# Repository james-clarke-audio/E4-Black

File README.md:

# E4 — "E4-Black"

An **STM32F411 micromouse**: a C++ port of the ukmars
[**mazerunner-core**](https://github.com/ukmars/mazerunner-core) firmware onto
custom hardware, with a **Web Bluetooth** companion app for live telemetry,
control and calibration. Built for the October 2026 micromouse competition.

> **Status:** active development — hardware bring-up and sensor calibration.

## Features

- **1 kHz control loop** (SysTick) — motion, sensing and the search brain all
  run deterministically.
- **IR wall sensing** — four emitter/detector pairs, ambient-subtracted with a
  batched dark-then-lit read. Two forward sensors (front wall) and two diagonal
  sensors (side walls / centring).
- **Gyro heading** — the gyro holds heading; the side sensors handle lateral
  position and wall presence. Gyro scale is **calibrated on the floor and
  persisted to EEPROM**, not compiled in — it is a property of the individual
  MPU-9250 and shifts with temperature, so it can be re-measured at a venue
  with nothing but the companion app.
- **On-board UI** — SSD1306 OLED with a two-button menu; the whole menu is also
  drivable over Bluetooth.
- **Bluetooth telemetry & control** via the companion app — a Control tab for
  watching and driving her, and a Tuning tab for setting her up: live IR
  monitor, an emitter-hold camera aid for aiming, live turn tuning (gyro-closed
  spins & arcs), and firmware-version reporting.
- **Non-blocking wall sampling** (opt-in) — a five-state sampler ticked from the
  control ISR returns a full ambient-subtracted set every 5 ms with no
  busy-wait, so the wall flags stay live while she's moving.
- **Maze persistence** to on-board EEPROM.
- **Flood-fill search / speed run** from mazerunner-core, with a virtual/real
  sensor switch so the brain can be exercised in simulation.
- **A route executor** — one walk that either drives a planned route or
  rehearses it, so the rehearsal proves the sequencing the driver uses.
- **Time-weighted route planner** — least time rather than fewest cells, with
  diagonals *searched* rather than substituted, and an optimistic twin of each
  plan that says how much is still left to find.
- **Wall follower**, both hands, driven and simulated — its own competition
  class rather than a fallback solver.
- **A simulator that runs at the speed the motion model predicts**, so a
  simulated run takes as long as it claims to and the two numbers can be
  compared. Playback can be sped up for watching; the reported figure never
  moves with it.
- **A maze editor in the companion app** — draw a course on the big canvas,
  save it as text or `.maz`, and send it straight to her. Quicker than hunting
  through 406 files for one that exercises the thing you are testing.

## Hardware

- **MCU:** STM32F411CEU6 (Cortex-M4F, "Black Pill"-class).
- **Wall sensors:** 4× IR pairs — TSAL6100 emitters (940 nm) into OP505A
  phototransistors; emitters switched low-side by FDV301N MOSFETs from a 5 V
  rail. (The original board carried SFH4550; the sensor assemblies now fitted
  are TSAL6100.)
- **Display / storage:** SSD1306 OLED and a 24LC256 EEPROM, both on I2C1.
- **Drive:** DRV8833 motor driver, plus a gyro for heading.

Full pin map, sensor geometry and housing detail are in the reference manual
(see below).

## Build & run

- **Firmware:** STM32CubeIDE (2.2 / GCC 14). Import `Source/` as an existing
  project, build the **Debug** config, and flash over ST-Link to the
  STM32F411CEU6.
- **Companion app:** open `e4-maze.html` in a Web Bluetooth browser — Chrome or
  Edge on desktop, or an iPad via a WebBLE browser such as Bluefy (iOS Safari
  has no Web Bluetooth). Pair over BLE to monitor the sensors, drive the menu,
  and read the running firmware version.
- **Hosted copy:** the repo publishes to GitHub Pages, so the current app is
  always live at
  [`/E4-Black/e4-maze.html`](https://james-clarke-audio.github.io/E4-Black/e4-maze.html)
  and the manual at [`/E4-Black/docs/`](https://james-clarke-audio.github.io/E4-Black/docs/).
  Web Bluetooth needs a secure context, so on a tablet this is the route to use
  rather than copying the file across.

## Documentation

The **E4 Reference Manual** lives in [`docs/`](docs/index.html) — open
`docs/index.html`. Eleven chapters: overview, architecture & pin map, sensor
aim, sensor geometry, sensor housing, the firmware/menu map, position integrity
("Staying Located"), a design note for the next board (STM32G474), how she
chooses her path, the turn table, and the sensor carrier.

## Repository layout

| Path | What it is |
|------|-----------|
| `Source/` | STM32CubeIDE firmware project (Core / Drivers / Modules / Program). |
| `CompanionApp/` | Native SwiftUI companion (macOS/iPad) + the `E4Core` package — **the tool she is driven from**. |
| `e4-maze.html` | Web Bluetooth companion app (single file); follows the Swift app rather than leading it. |
| `docs/` | The reference manual (`index.html` + chapters). |
| `3D Files/` | Sensor housings, wheels, mounts, and the sensor socket plate (STL, print notes, and the parametric source that generates and verifies it). |
| `tools/planner-bench/` | Native build of the route planner, for scoring routes against the maze files without a robot. |
| `tools/bench-mazes/` | Finds and writes the per-turn tuning rigs, and checks the shipped files by planning them. |
| `mazefiles/` | 408 real competition mazes, binary and text, plus `bench/` — twelve single-corridor tuning rigs. |
| `E4-cell-alignment-A4.pdf` | 1:1 print jig for squaring a test cell. |

See [CONTRIBUTING.md](CONTRIBUTING.md) for the fuller layout and workflow.

## Contributing

`main` is protected: collaborators work on a branch and open a pull request.
Details, commit style and the firmware-version convention are in
[CONTRIBUTING.md](CONTRIBUTING.md).

## Credits

Firmware is a port of Peter Harrison's ukmars **mazerunner-core**. Thanks to the
UK micromouse community.

## License

Released under the [MIT License](LICENSE) — © 2022 Peter Harrison
(ukmars mazerunner-core), © 2026 James Clarke. E4 is a derivative of the
MIT-licensed mazerunner-core and keeps the same terms.

---

## Firmware releases

`FW_VERSION` lives in `Source/Program/inc/version.h`, shows on the OLED splash
and is reported over Bluetooth (`VER?`). **Minor** for a feature, **patch** for
a fix. **1.0.0 is reserved** for the build that goes to the October competition
— everything before it is bring-up.

Each entry names the firmware commit; companion-app and docs commits that
landed alongside are listed after it, since the two move together. Newest
first.

**0.34 — 18 Sep 2026 · The post loop**
From an old lab note of James's: drive into a cell, then round a post
continuously, watch the centre drift and adjust α. It is a better rig than the
zigzag, and one line of geometry says why.

**Four chained same-hand 90s of radius 90 *are* a circle centred on a post.**
She comes up the lane at x = 90 turning right; the arc centre sits 90 mm to her
right, which is the post. After the quarter she is heading east and her right is
now south — the same point. Every quarter shares a centre, so the four are one
circle, 565.5 mm round.

Which pins ω: `R = v/ω`, so R = 90 at 300 mm/s needs **191 °/s** — the figure
`SS180` already holds, because its lateral step of 2R is also one cell. And it
reconciles the two numbers in Ch 10: **226 is the figure for a turn driven on
its own**, where ω ramps to zero at the end and the trapezoid swings wider than
the ideal circle. Driven continuously there are no ramps between the quarters,
so the ideal `R = v/ω` applies and 191 is simply right. Two manoeuvres, two
answers, and the loop is the one that matches what a chained turn has to be.

**It separates ω from α.** Over a closed lap the four local frames sit at 0°,
90°, 180° and 270°, so any consistent per-turn displacement error sums to zero —
radius, offsets, tangential lag alike. Heading does not: the frames precess, the
lap stops closing, and the centre walks by about `2.83·|d|·ε`.

| error per turn | drift per lap | after 8 laps |
|---|---|---|
| 0.1° | 0.6 mm | 5 mm |
| 1.0° | 6.3 mm | 50 mm |

So ω sets the *size* of the circle and α sets the *drift* of its centre. It is
also the honest gyro-scale test — at running speed with the wheels rolling
rather than scrubbing in place — and the two causes separate, since scale error
is speed-independent while α's grows with ω. Odometry gives the radius back for
nothing: arc distance over 2π·laps, reported as `R_meas` beside the 90 it wants.

`Post loop` (Calibration, or BT `A`), set up by `LOOP,laps,ω,α,hand,speed`. It
is its own menu action rather than another use of `ARC` because **1440° is not a
turn** and writing it into a row would ruin the row.

*Alongside:* page 15 of `E4-bench-diagnostics-A4.pdf` draws the rig — a 2×2
block with the middle post free-standing, the 90 mm circle to mark round it, the
tangent run-in, and what a degree per turn looks like after one, four and eight
laps. Her outline on every page is now the real one: the chassis board is 77
wide with wheel wells stepping in to 11.46/65.54, 100 long with a semicircular
nose of radius 38, and the axle 35 mm from the back — all of it already written
down in Ch 11, Ch 4 and `config.c`.

**0.33 — 18 Sep 2026 · The approach is part of the turn**
A tuning run is *drive to the turn, make it, drive out* — and the first of those
three was the one the tuner could not be asked for. `ARC`'s fifth field writes
`entry_offset`, and `run_arc_from_table()` passed `entry_offset` straight in as
the lead-in, so the arc always began that many millimetres after she started
moving. Fine for "does this arc look right"; useless for "does she come out of
it in the lane", which is the only question a bench answers.

The approach is now counted in cells and the millimetres derived:

| entered from | lead-in |
|---|---|
| a straight | `BACK_WALL_TO_CENTER + cells × FULL_CELL − entry_offset` |
| the diagonal | `cells × DIAG_PITCH − entry_offset` |

`DS45`, `DS135` and `DD90` begin **on** the diagonal, where the pitch is 127.279
and there is no back wall to square up on — she is placed on the line by hand.
Which case applies follows from the row rather than from a switch someone has to
remember: a turn that leaves the diagonal is a turn that was already on it.
`POS,<cells>` sets it, `TUNE,pos=,lead=,pitch=` reports what she will actually
drive *before* anything moves, and `TURNRES` carries the row and the lead so a
log line three runs back still means something.

**The card does the arithmetic before she does.** `R = v / ω`, and an arc joining
two lanes that cross at θ is tangent to both only at `R·tan(θ/2)` either side of
the crossing. There is one wrinkle, and it took drawing the maze out 1:1 to see
it: `entry_offset` is measured back from the **lattice point** the planner books
the turn at, which for most turns is also where the two lanes cross — but an
`SD45` is booked in at a **cell centre**, while a straight lane meets a diagonal
at the **wall midpoint 90 mm earlier**. That half cell is part of the offset.

| row | ω | R at 300 | tangent | + half cell | needs | has | |
|---|---|---|---|---|---|---|---|
| SS90E | 170 | 101 | 101 | — | 101 | 100 | agrees |
| DD90 | 273 | 63 | 63 | — | 63 | 63 | agrees |
| **DS45** | **95** | **181** | **75** | **—** | **75** | **120** | **does not** |
| **SD45** | **95** | **181** | **75** | **90** | **165** | **120** | **does not** |

So the two 45 rows cannot both be right while they share a number — one needs
165 and the other 75. The same 120 sits in the planner as `sd45_offset` /
`ds45_offset`, so those move with them. The Tuning screen shows the gap and
offers the figure; the floor decides which of the numbers was wrong, but it
cannot until they agree.

One number says it best: a diagonal step is 127.3 mm and `ds45_offset` is 120 of
it, so on `bench-3x3-45min` the DS45 gets **seven millimetres** of approach
before the arc starts. At the tangent value it gets 52. That is why the planner
abandons that geometry and drives `ARC_R, SPIN_L` instead.

*Alongside:* `E4-bench-diagnostics-A4.pdf` — the 1:1 cell template (centrelines,
corner-to-corner, and the diamond joining the four wall midpoints that is the
actual diagonal lane), plus a page per hand showing where the mouse gets put
down. `06fc12d` and `fa6d585` — `mazefiles/bench/`, twelve single-corridor
tuning rigs, and `tools/bench-mazes/` which found them by enumerating every
corridor that fits in a section and asking the real planner what each one
produces. Two results fell out of that search. A 3×3 entered at (0,0) facing
north can only turn right first, because the west perimeter is beside her —
`SD45_L` is unreachable there without a spin. And **(2,0) facing north is the
mirror image of (0,0) facing north**, so once the start pose is allowed to move,
every left-hand rig is the x-mirror of its right-hand twin, walk for walk.

**0.32 — 18 Sep 2026 · She can finish by turning into the goal**
Every goal test in `plan_native()` sat inside the cell-expansion loop, which
advances a cell *before* it looks. So a route that **arrives** at the goal by
turning into it was never recognised as finished: she drove past and came back,
or took a longer way round that happened to approach along a straight.

The node's own cell is now tested before the loop, with `best_cells = 0` and
`best_t = 0` because the turn that brought her there is already paid for in
`key`. `step_time()` returns `0.0f` for a zero-cell goal step rather than asking
`straight_time()` for a negative distance — the clock stops on *entering* the
goal, and what is left of that cell afterwards is not on it.

On Boston the last vertices went from `DS45_L (17,18) → (17,17) → GOAL (17,15)`
to `… → GOAL (17,17)`. Swept over the whole 394-maze corpus: **72 faster, 320
unchanged, 2 slower, 0 invalid**, mean 32.864 → 32.761 s. Best: japan1997f
−3.460 s, uk1992q −2.698 s, boston −1.544 s.

The two slower ones are not a regression in the fix. `key_of()` quantises time
to centiseconds — that is what makes Dial's bucket queue O(E) — so routes tying
on the quantised key can differ by up to ~10 ms a step, and ≤0.13 s over twenty
steps is inside one bucket width. Recorded here so nobody hunts it later.

**0.31 — 18 Sep 2026 · No toy maze at boot, and the editor can undo**
The boot scaffold seeded a two-cell maze with the goal at (1,1). It made a whole
class of mistake invisible: a Plan route run with **no maze sent** looked
entirely successful, because there really was a maze and she really did solve
it. She now boots with `maze.h`'s own `m_goal{7, 7}` and an open arena as ground
truth, so a run with nothing sent looks like what it is.

The companion app's maze editor grows undo — `history: [E4MazeFile]` with
`canUndo` / `undo()`, and ⌘Z on the canvas.

**0.30 — 17 Sep 2026 · She speeds up through ground she has already covered**
Watching a simulated explore, she never went any faster in cells she had already
been through — and she didn't, in either the simulator or the firmware.
`sim_move_seconds()` used `FULL_CELL / SEARCH_SPEED` for every cell, and
`search_to()` crawls at `SEARCH_SPEED` from the first cell to the last. The
simulator was faithfully showing what the firmware does, which is the simulator
doing its job.

**The test is per cell, not per leg.** The obvious version of this is to run the
whole return leg fast, on the grounds that she has just driven it. That is
wrong: the flood picks the best *known* path home and known does not mean
*visited* — she will have seen a cell's walls from next door without ever
entering it, and those cells are exactly where there is still something to
learn. So the return leg becomes an exploring run that happens to be quick in
the parts already covered.

`cruise_speed()` is that rule, in one place, used by the driven search and the
simulated one so neither models something the other does not do:

| condition | speed |
|---|---|
| the cell she is **entering** is fully visited, **and** the move out of it is straight | `RUN_SPEED` |
| anything else | `SEARCH_SPEED` |

The second condition is the one that is easy to forget. There is no room to shed
speed between a cell's sensing point and the turn point after it, so carrying run
speed into a turn means entering it too fast. Checking costs nothing: in visited
territory the map is complete, so `heading_to_smallest()` on the flood she
already has is a reliable one-cell look ahead.

**And a sloppy read at speed cannot hurt her**, which is what makes this safe
rather than merely fast. She still senses and still calls `update_map()` in a
cell crossed at 600 mm/s — but `update_wall_state()` refuses to change a wall
that has already been seen, and *fully visited* means every wall in that cell
has been. A bad reading is discarded by construction, in exactly the cells where
the rule allows speed. The only place a wrong wall could be written is a cell
with something unknown in it, and those are the cells she is required to crawl
through.

`sim_move_seconds()` now tracks the speed she is **carrying** and costs each move
with `timing::straight_time` — the planner's own model — so a run of visited
cells visibly winds up and the cell before a turn visibly sheds it, instead of
every cell costing a flat 0.6 s.

The wall follower stays at search speed throughout, deliberately: `cruise_speed()`
reads the flood to look ahead, and a follower never floods.

**0.29 — 17 Sep 2026 · The executor left a diagonal by the wrong side**
A diagonal speed run finished at **(1,0)** — near the start, nowhere near the
goal — having walked a staircase west and south with no 45° heading in it, on a
route whose time came back exactly right at 23199 ms.

One line. `run_route` left a diagonal with `nh = (L) ? ((dd + 3) & 3) : ((dd + 1) & 3)`.
"+3 to turn left" is correct *inside* an enum. This crosses from `Diag` to
`Head`, and those are different enums offset by half a turn: leaving a diagonal
to the left is **+0** and to the right is +1. The right hand was accidentally
correct, which is why it took a real route to expose.

What it does is worse than a wrong heading: it lands her on a **post**, the one
lattice point that is never occupied, so her half-cell coordinates lose their
parity and every orthogonal move afterwards keeps her on the wrong parity for
the rest of the route. Hence a whole run animated on the lines *between* cells —
which is exactly what the `POS` trail showed, every coordinate an even multiple
of 90.

Fixed in **one place, not two**: `diag_ccw`/`diag_cw` move from statics in
`native.cpp` to inline functions in `native.h`, so the executor uses the same
mapping `route_points()` does rather than a second copy of it. Two copies of that
mapping is how one of them went wrong.

And the walk checks itself now. A route ends at a cell **centre**, odd in both
half-cell coordinates; anything else means the walk lost the lattice and every
cell it has reported since is fiction. It says so — `SR,LOST u= v= diag=` —
rather than reporting a plausible wrong answer.

Verified on the maze that broke it: every vertex of the run now matches the
planned route exactly, and she finishes at (8,8).

**0.28 — 17 Sep 2026 · The route executor**
The planner has been able to answer since 0.20 and nothing acted on the answer.
`run_route()` does.

**One walk serves both the real run and the rehearsal.** The part worth getting
right is the sequencing — which turn, after how many cells, from which heading —
and a simulator that sequenced differently from the driver would prove nothing
about the driver. The only thing the `simulate` flag changes is whether a step
is animated or driven.

Timing comes from a new `route_times()` in `diagonal.cpp`, which walks the route
with the **same `step_time()` that costed it** and reports each step split into
the run before the turn and the turn itself. That split is what lets the
rehearsal animate a step at its true duration, and it means the simulated total
equals `route.seconds` by construction rather than by coincidence.

    Sim speed run   F    plan, then rehearse at the speed the model predicts
    Speed run       l    plan, then drive
    KIND,<0|1|2>         shortest · quickest · quickest with diagonals

Which route is a **setting** rather than three menu entries, because the three
are one run with a different cost function and the point is comparing them back
to back on one maze. The default is quickest orthogonal: the diagonal route is
faster on paper, but every diagonal row of the turn table is arithmetic that has
never met a floor.

Both actions **stream the route before executing it**, so the line she is about
to take is on screen before she takes it, and a run that goes wrong can be
compared against what she meant to do rather than against memory.

One simplification, named in the code rather than hidden: in the simulated turn,
position advances during the run and heading rotates at the vertex, so an arc
looks like a spin on screen. The *time* is right either way and the route line
shows the true path — but the animation is not evidence about arc geometry.
**Zigzag test** is what answers that.

> `act_speed_run` is **unproven**. No part of the driven path has been near a
> floor, and the turn table it reads is arithmetic outside the two SS90E rows.
> It arms and waits like everything else; give her room.

**0.27 — 17 Sep 2026 · The followers arm like everything else, and say so**
Two bugs, both from 0.25. `follow_to()` **did not wait** — every other action
that turns a wheel calls `sensors.wait_for_user_start()` before it moves, and
the driven wall follower went straight from a tap in the app to driving. It arms
now, and so does the simulated twin, so both halves of the pair behave the same
way and neither teaches a habit the other punishes.

The four followers were also missing from `waitsForButtonPress`, which is why
pressing one in the app looked like nothing happening: she printed
`armed: press a button to launch` and blocked, correctly, and the app had no way
to tell a deliberate pause from a dropped command. Both apps now put that
message in front of you rather than leaving it as one line among hundreds, and
the **Actions** screen gets the same armed banner the maze screen already had —
it had been showing `Running:` for an action doing nothing of the sort.

**0.26 — 17 Sep 2026 · The simulator runs at the speed the model predicts**
`sim_step` animated eight frames of thirty milliseconds whatever the move, so a
cell crossing, a 90 and a dead-end reversal all took 240 ms and the simulator
told you nothing about time. It takes a **duration** now and the frames follow
from it, and that duration comes from `timing.h` — the planner's own model, not
a second one written for the animation, so the two cannot drift into different
opinions about the same mouse.

| move | cost |
|---|---|
| `AHEAD` | one cell at search speed |
| 90 | an **arc**: she rotates *while* she travels, so it is whichever of the two takes longer, not the sum |
| `BACK` | the one move that does not overlap — `turn_back()` stops dead, spins on the spot and moves off again, so that one adds up |

Getting the 90 wrong the other way is how a simulator flatters a route full of
corners; getting `BACK` wrong is how it flatters one full of dead ends.

The reported time is now the **modelled** clock, not `HAL_GetTick()`. The two
agree to within the odd frame, which is exactly why the wall clock must not be
the one reported — a slow link or a stalled frame would read as a slower mouse,
and the figure would stop being a property of the route. Real search runs are
untouched; there the wall clock *is* the truth.

Two details decide whether it is honest. The frame deadline **absorbs** transmit
time rather than adding to it (a `POS` and `TEL` pair is about 56 bytes, roughly
10 ms of wire at 57600, so delaying a full frame on top would run every run a
third slow). And `SIM_RATE` — `SIM,<rate>` over BT, a picker in both apps —
scales the *watching* only, because a real-time explore is forty-odd seconds and
nobody should sit through that twice, but the number she reports must not move
when you skip ahead.

**0.25 — 17 Sep 2026 · The wall follower, both hands, driven and simulated**
`follow_to()` had been sitting in `mouse.h` implementing a left-hand follower the
whole time, with `act_wall_follow` still an `act_todo` stub, so nothing could
reach it. It takes a hand now:

    20  Wall follow L   w        32  Wall follow R   W
    33  Sim follow L    q        34  Sim follow R    Q

Four entries rather than one action with a hand setting, because the hand *is*
the experiment — left and right walk different halves of a course. The
simulated pair animate the same decision with the motors never armed, so both
hands can be run against any maze file with no bench at all.

**A wall follower is its own competition class, not a weaker solver.** A
follower course is built with a wall connected all the way to the centre, so a
follower always arrives — that is the point of the event. A maze-solver maze is
built the other way round, with the inside deliberately disconnected from the
outside, so a follower can never reach the middle of one however long it walks.
Same code, two events.

So `FOLLOW_STEP_LIMIT` (512, four times the cells in the arena) is not a guard
against a weak algorithm — on its own course it never trips. It exists because
this code gets pointed at a solver maze in the simulator, where **not arriving
is the correct answer**, and the only wrong behaviour would be walking for ever
while that is true. Giving up reports `WF,gave up after N cells (left hand)`.

Of the **406** files in `mazefiles/binary`, **90 are follower-solvable and 316
are not** — and it is the *same* 90 for both hands, with not one maze yielding
to one hand and not the other. That is structural rather than luck: the hand
decides which route she walks, not whether the centre is reachable. If the
centre's walls are connected to the perimeter, both hands are walking the same
wall component; if it is an island, neither can. Five of the 90 are built for
the class explicitly — `uk2010follower`, `uk2011follower-final`,
`tic05followersheats`, `robotic-2011-follower-heats`, `-finals` — and 33 are
competition mazes including `japan1991`, `uk2003q` and `uk2009f`. `test3.maz`
arrives in 14 cells if you only want a smoke test.

**0.23 — 16 Sep 2026 · How much of the route is still guesswork**
"Have I explored enough?" had no answer but a feeling. It has one now, and it is
a proof rather than a percentage.

`act_plan_route` already flips the wall mask, so the second plan is nearly free.
`MASK_CLOSED` treats an unseen wall as a wall and yields the best route she can
**prove**. `MASK_OPEN` treats it as an opening and yields the best route that
could **possibly** exist — a true lower bound, because the real maze has at
least as many walls as the optimistic view of it. The gap between them is the
most that is still out there to find, and when it closes her route is not
probably the best, it **is** the best and no further exploring can change it.

The cells worth driving to are exactly the not-yet-fully-seen cells *on* the
optimistic route. That is the sharp version of "explore what is left": an
unknown cell no optimistic route passes through cannot change the answer,
however blank it looks on the screen. A long corridor whose north walls she
learned from driving the row above, and whose east–west state she knows nothing
of, only matters if the best possible line wants to go down it.

    RB,<kind>,<ms>,<unknown cells on that route>
    RU,<x>,<y>  …  RUE,<total>        the union — and only these matter

The union is taken across all three kinds deliberately: it is a superset of what
an orthogonal-only run needs, which is the safe direction to be wrong in while
the diagonal arcs are untuned.

`route_cells()` in `native.cpp` walks a route and emits every **cell** it
covers, which is a different set from `route_points()`' corners — a six-cell
straight is two points and six cells, and a diagonal step is no point at all but
does cross one cell. The OLED shows known, best possible and the unseen count,
and reads `PROVED` when there is nothing left; both apps draw the unseen cells
as dashed amber squares under the route lines.

**0.22 — 16 Sep 2026 · Fast-run speeds, separate from the search speeds**
`act_plan_route` built its `Robot` from `SEARCH_SPEED` and `SEARCH_ACCELERATION`,
so it was planning the **fast run at search speed**. That is why `SHORTEST` and
`QUICKEST` came back at 27.245 s each with identical point lists on the bench
mouse: told that a straight is no quicker than a corner, the planner has nothing
to choose between.

Search speed is bounded by sensing — she reads walls and decides where to go
once per cell — and is settled at the bench. The fast run has no such limit,
because the map is already known.

    RUN_SPEED         600 mm/s     twice the search speed, a timid opening bid
    RUN_ACCELERATION  2000 mm/s²   as the search, until it is measured
    RUN_DIAG_SPEED    300 mm/s     the diagonal corridor is 110.3 mm between
                                   posts against 168 down a cell — about 14 mm
                                   a side with the plate on. She threads it.

The **arc** speeds are untouched and stay as the turn table holds them. They are
independent: she can run a six-cell straight flat out and still take every SS90
at the speed its row was tuned at, and that independence is the whole mechanism
by which a longer, straighter line starts to beat a shorter, twistier one.

Runtime rather than `const`, like the turn table and the spin dynamics — `SPD?`
and `SPD,v,a,diag` over BT, persisted as config block **v6**. Nothing drives on
them yet (`act_speed_run` is still a stub), so a wrong value costs an estimate,
not a mouse.

Sweeping the straight speed across the full competition mazes says where her lap
time actually lives:

| `v_max` | 300 | 600 | 1000 | 1500 |
|---|---|---|---|---|
| tricky.maz | 67.83 s | 51.93 s | 47.87 s | 46.80 s |
| APEC2017.maz | 71.97 s | 52.39 s | 46.93 s | 45.02 s |

300 → 600 buys 23%. 600 → 1500 — two and a half times the straight speed — buys
another 10%. The routes are **turn-dominated**: sixteen arcs at 300 mm/s swamp
what the straights can save, so the turn table is worth more bench time than the
straight-line number.

Two fixes landed with it. `act_plan_route` was planning to a **1×1 goal** when
the goal is a 2×2 room, so she drove *through* two goal cells to reach the one
square she had been told to reach — work done after the clock had already
stopped. And the app was never sent the **perimeter**: `maze.initialise()` walls
the outside of the arena before a single sensor reading, but `W` lines are only
sent for cells she stands in, so the border was known at both ends of the link
and sent over neither.

**0.21 — 16 Sep 2026 · The planner reaches the app**
`Plan route` (Maze solver, or `P`) runs the planner three ways over the map she
is currently holding — shortest, quickest, quickest-with-diagonals — and streams
each to the companion apps, which draw all three over the same maze. No motors,
so it works on an injected maze, a remembered one, or one she has just explored:
a whole run can be rehearsed at the bench before she drives a cell of it.

Points go out in **half-cells**, which is the unit the planner's lattice already
works in. Cell centres land on odd coordinates and wall midpoints on mixed ones,
so a diagonal arrives at the app as an ordinary pair of points — neither
companion has to know about the lattice, the parity rule, or which wall a point
sits on. Draw a polyline through them and it is right.

    RT,<kind>,<ms>                      kind 0 shortest, 1 quickest, 2 diagonal
    RP,<u>,<v>,<move>                   a vertex in half-cells
    RTE,<points>,<cells>,<turns>,<spins>

The firmware carries only `native.cpp`: with diagonals disabled it *is* the
orthogonal planner, and `tools/planner-bench/xcheck` confirms the two agree in
shape on all 392 mazes. That keeps `planner.cpp`'s 36 KB out of the build.

Both apps also gain **Zigzag test** and the `ZIG,turns,mode,first` setup, so the
chained-arc question can be settled without the OLED.

Documented in [Ch 12 — Planning the Fast Run](docs/e4-planner.html); the
[Build Map](docs/e4-build-map.html) now shows the diagonal capstone as half
done — the planner is shipped, the 45° *motion* is what is left.

**0.20 — 16 Sep 2026 · Diagonals, searched rather than substituted**
`native.cpp` puts the diagonal moves into the graph and searches, instead of
planning orthogonally and rewriting afterwards. Work in half-cells and parity
says what a point is — (odd,odd) a cell centre, mixed a wall midpoint,
(even,even) a post — and a diagonal is a straight line through wall midpoints
stepping ±1,±1, so it never lands on a post. It is *not* the line joining cell
centres diagonally: that goes straight through one. Because it searches, it can
take a **longer** cell route because that route diagonalises better, which is
the one thing post-processing can never do.

Across 392 real competition mazes, against the orthogonal quickest route:
classic substitution **−3.4%**, native search **−13.2%**, best −47.6% on
`quo4`.

`route_check()` walks a route over the lattice against the map, independently
of whichever planner produced it — because the two disagreed and a planner that
scores its own output is only as honest as its own model. It found that classic
was reporting times for routes she could not drive: the exit hand off a
diagonal is fixed by the lattice rather than by the zigzag, and the diagonal
does not end in the cell the zigzag ended in. Fixing both took classic from a
claimed 8–10% to a real 3.4%. Both methods now pass on all 392.

Documented in [Ch 12 — Planning the Fast Run](docs/e4-planner.html). Still
nothing calls any of it, so there is still no speed run.

**0.19 — 16 Sep 2026 · A route planner, and a test to prove it wrong**
Two new modules that nothing drives yet, and one bench routine that exists to
settle an argument between them and the firmware.

`planner.cpp` answers *least time* where the flood in `maze.h` answers *fewest
cells* — a different graph, not a replacement. Time is not additive per cell
(she accelerates, so four one-cell moves and one four-cell straight differ), so
nodes are turns rather than cells and an edge is "run N cells, then turn". The
FIFO had to go with it: a plain queue is correct only while every edge costs
the same, which is what unit cost bought. It is Dial's algorithm now — a
circular bucket queue, still O(E), with a guard that invalidates the plan
rather than clamping if an edge outgrows the ring.

`diagonal.cpp` does classic diagonal substitution on the result, costing every
candidate both ways and substituting only when the diagonal actually wins.
**Worth 3.4%** across 392 real competition mazes. An earlier version of this
entry claimed 8–10%; that figure came from routes she could not have driven,
and is corrected in 0.20.

**Zigzag test** (Calibration, or `Z`) drives N alternating 90s in consecutive
cells with no straight between, ending stopped at a cell centre so the offset
can be measured. It is there because the planner and `turn_smooth()` disagree:
at R = v/ω ≈ 101 mm two arcs one cell apart need 202 mm and have 180, so the
planner refuses and emits stop-and-spin — while `turn_smooth()` relabels the
frame past the next turn point and simply runs the arcs back to back. `ZIG,` over
BT sets turns, mode (chained arcs or spins) and first direction. Whichever way
it comes out, one of the two is wrong and the 8–10% diagonal figure moves with it.

Neither planner module is called by anything; `--gc-sections` drops all 36 KB
of the planner's working set until something does.

**0.18 — 13 Sep 2026 · Connecting greets her, not drives her**
The app asked for the firmware version by *running the menu action*, which
parks on the OLED waiting for a button press — on a screen nearly identical to
the boot splash, so she read as hung, and the menu cursor was left sitting in
Diagnostics. Replaced with a `VER?` query that answers without touching the
menu.
`f9c32fd` · tests `9a5f6d8`

**0.17 — 13 Sep 2026 · The whole configuration, on demand**
`CFG?` dumps every persisted value — gyro scale, the three wall thresholds, all
sixteen turn rows and the spin dynamics — so the app can show what she is
actually running rather than what it last sent her.
`246aeec`

**0.16 — 13 Sep 2026 · Spins join the table**
`OMEGA_SPIN_TURN` / `ALPHA_SPIN_TURN` become runtime values: tunable over
Bluetooth (`SPIN,…`) and saved with everything else. Config block goes to v5.
`9c71672`

**0.15 — 13 Sep 2026 · Slots for the diagonal set**
The turn table grows from four rows to the full sixteen — SS90E, SS90, SS180,
and the diagonal entries and exits (SD45, DS45, SD135, DS135, DD90), left and
right. The diagonal rows carry computed geometry and sit inert until the
diagonal solver exists.
`6bc5987` · docs `d1c8ef4` (Ch10, the turn table)

**0.14 — 13 Sep 2026 · One turn, tunable live, saved to EEPROM**
There were three separate copies of the same 90° turn and they had already
drifted apart — the menu ran alpha 1000 where the search brain ran 2500.
Collapsed into a single `turn_params[]` table that the menu, the search brain
and the tuner all read from, editable over Bluetooth and persisted.
`4f0f4d1`

**0.13 — 13 Sep 2026 · Show what is running, on both displays**
Commands sent from the app bypassed the menu, so the OLED carried on showing
something else entirely. The menu cursor now follows whatever action actually
runs, wherever it was started from.
`d339d11` · app `f2d5cd0`, `11cd734`, `b323651`, `b828179`, `108e0c8`, `382c723`
(threshold calibration drawn rather than described; session replay)

**0.12 — 13 Sep 2026 · Threshold calibration: the third capture**
Two captures — walls present, walls absent — cannot describe a corridor, where
the sides see wall and the front does not, which is the state she spends most
of her life in. Added a third capture and generalised the margin test to
weakest-present against strongest-absent.
`93a3c9c` · app `ee8095a`, `02bf440`, `167dc30` (maze file import and upload)

**0.11 — 12 Sep 2026 · Per-sensor wall thresholds, calibrated and persisted**
One shared side threshold became `WALL_THRESH_LEFT` / `_RIGHT` / `_FRONT`,
settable over Bluetooth (`THR,l,r,f`), captured by a guided routine and saved
to EEPROM. Also fixed the EEPROM self-test, which had been writing its scratch
pattern to address 0 — over the maze store.
`12142da` · app `3dbdb43` · docs `7b189fa` (Ch9, how she chooses her path)

**0.10 — 11 Sep 2026 · One-press Bluetooth bring-up**
A replacement module can be provisioned from the menu — name set to `MMOUSE`,
baud to 57600 — with no serial adapter and no guesswork.
`8c0b13a` · app `64b5e6f`, `2ce5fc9`, `2a243a9`, `29ccaab` (the native SwiftUI
client starts here: sidebar, seven screens, session logging)

**0.9 — 11 Sep 2026 · Gyro scale becomes a runtime value**
`GYRO_SCALE` moves out of the source and into the config store: spin a known
angle, send the error, save. It is a property of the individual MPU-9250 and
shifts with temperature, so it has to be re-measurable at a venue with nothing
but the app.
`f03e0b8`

**0.8 — 10 Sep 2026 · Non-blocking IR sampler**
A five-state sampler ticked from the control ISR returns a full
ambient-subtracted set every 5 ms with no busy-wait, so the wall flags stay
live while she is moving.
`1498a93` · app `daa2db3`, `2e7a50a` · repo `2fcd708` (CODEOWNERS), `1c77a9d`

**0.7 — 9 Sep 2026 · Live turn tuning over Bluetooth**
`act_turn_tune` stops being a stub: parametric in-place spins and arcs run on
command and stream back the achieved gyro angle and forward distance, so turn
dynamics can be tuned against the surface she is actually on without
reflashing.
`3ae1b6e` · app `910cb1b` · docs `e2a6766` (Ch7), `381987e` (Ch8)

**0.6 — 8 Sep 2026 · Batched IR read, ADC timing, menu tools**
Two-phase batched wall read (dark, then per-emitter lit) and IR sample time
raised from 3 to 28 cycles. First release with a stamped version.
`63e09fa` · app `2f60ad7` · docs `c0be1df` (the manual moves into the repo)

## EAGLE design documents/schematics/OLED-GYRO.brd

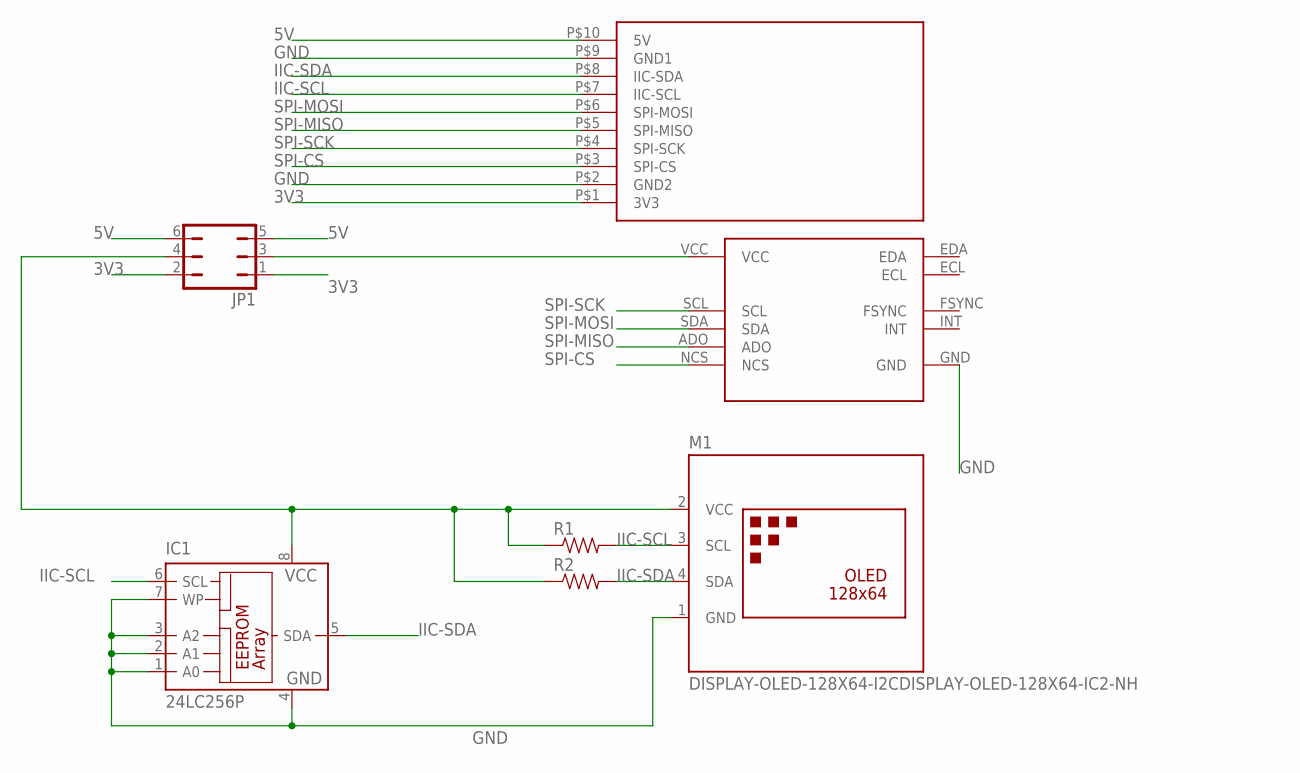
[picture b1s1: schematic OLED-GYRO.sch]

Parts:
IC1: 24LC256P; DIL8
JP1: JP3Q
M1: DISPLAY-OLED-128X64-I2CDISPLAY-OLED-128X64-IC2-NH; DISPLAY-OLED-128X64-I2C_NH
R1, R2: RESISTORPTH-1/4W; AXIAL-0.4
U$1: E4_SPI-IIC
U$2: MPU-9250/6500; MPU9265

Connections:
3V3: JP1.1, JP1.2, U$1.P$1 (3V3)
5V: JP1.5, JP1.6, U$1.P$10 (5V)
GND: IC1.1 (A0), IC1.2 (A1), IC1.3 (A2), IC1.4 (GND), IC1.7 (WP), M1.1 (GND), U$1.P$2 (GND2), U$1.P$9 (GND1), U$2.GND
IIC-SCL: IC1.6 (SCL), M1.3 (SCL), R1.P$2 (2), U$1.P$7 (IIC-SCL)
IIC-SDA: IC1.5 (SDA), M1.4 (SDA), R2.P$2 (2), U$1.P$8 (IIC-SDA)
unnamed: JP1.3, U$2.VCC
unnamed: IC1.8 (VCC), JP1.4, M1.2 (VCC), R1.P$1 (1), R2.P$1 (1)
SPI-CS: U$1.P$3 (SPI-CS), U$2.NCS
SPI-MISO: U$1.P$5 (SPI-MISO), U$2.ADO
SPI-MOSI: U$1.P$6 (SPI-MOSI), U$2.SDA
SPI-SCK: U$1.P$4 (SPI-SCK), U$2.SCL

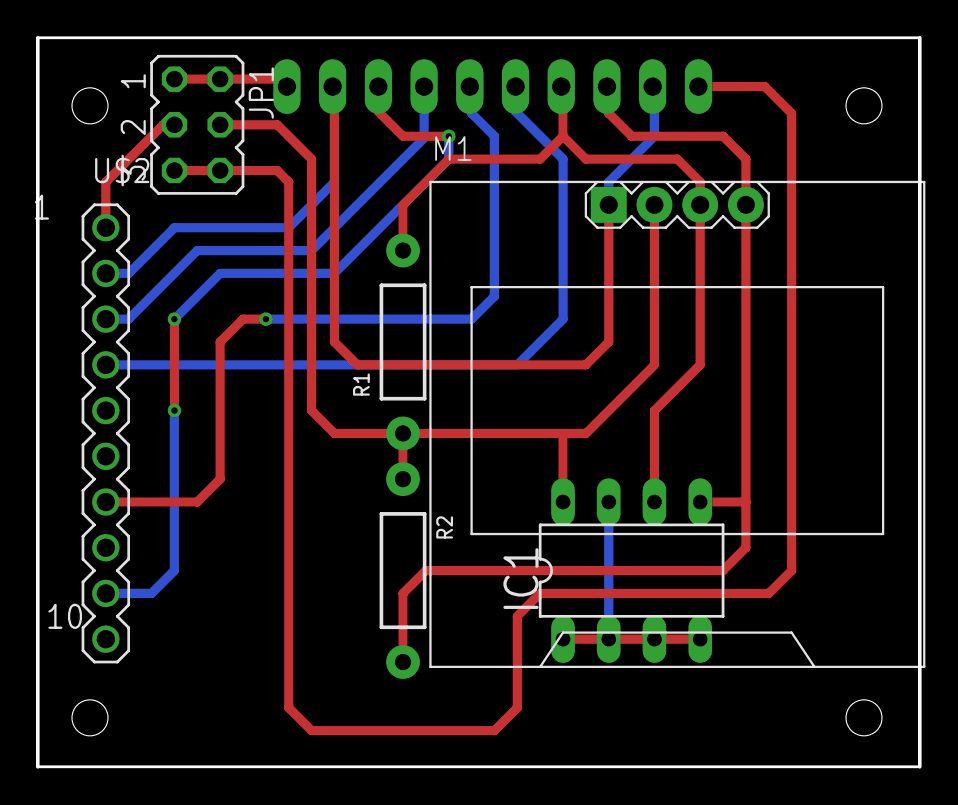
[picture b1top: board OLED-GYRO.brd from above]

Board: 2 copper layers, 49.0 x 40.5 mm, 7 parts (0 on the bottom side), 11 nets.

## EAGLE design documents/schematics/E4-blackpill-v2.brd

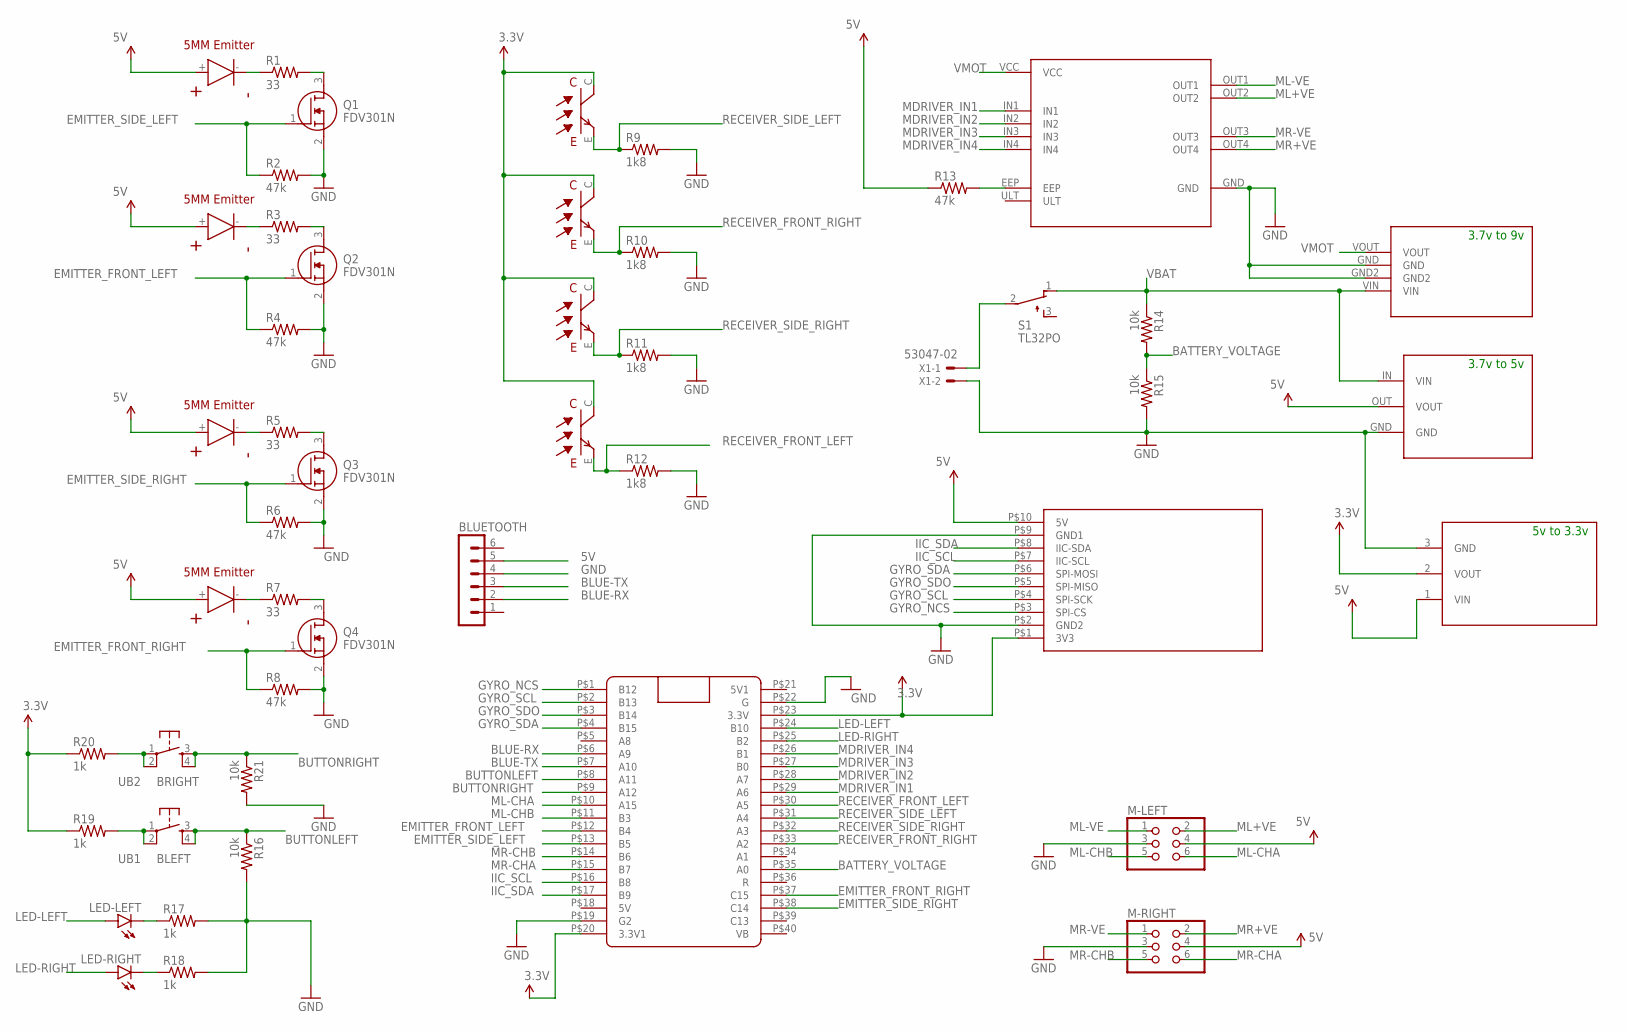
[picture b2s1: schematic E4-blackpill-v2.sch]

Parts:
BLUETOOTH: MA06-1
DET-FRONTLEFT: RECEIVER
DET-FRONTRIGHT: RECEIVER
DET-SIDELEFT: RECEIVER
DET-SIDERIGHT: RECEIVER
IR-FRONTLEFT: EMITTER
IR-FRONTRIGHT: EMITTER
IR-SIDELEFT: EMITTER
IR-SIDERIGHT: EMITTER
LED-LEFT: LEDSML0603; SML0603
LED-RIGHT: LEDSML0603; SML0603
M-LEFT: PINHD-2X3; 2X03
M-RIGHT: PINHD-2X3; 2X03
Q1, Q2, Q3, Q4: FDV301N; SOT96P237X111-3N
R1, R3, R5, R7: 33; 1206
R2, R4, R6, R8, R13: 47k; 0603-RES
R9, R10, R11, R12: 1k8; 0603-RES
R14, R15, R16, R21: 10k; 0603-RES
R17, R18, R19, R20: 1k; 0603-RES
S1: TL32PO; TL3XPO
U$1: E4_SPI-IIC
U$3: DRV8833
U$4: BUCK3TO9BUCK3TO9-HORIZONTAL; BUCK3TO9-HORIZONTAL
U$5: BUCK3TO5; BUCK3TO5-H
U$7: BLACK_PILL
U$8: 3V3-CONV3V3CONV; 6410-03
UB1: BLEFT; TACTILE-PTH
UB2: BRIGHT; TACTILE-PTH
X1: 53047-02

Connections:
3.3V: DET-FRONTLEFT.C, DET-FRONTRIGHT.C, DET-SIDELEFT.C, DET-SIDERIGHT.C, R19.1, R20.1, U$1.P$1 (3V3), U$7.P$20 (3.3V1), U$7.P$23 (3.3V), U$8.2 (VOUT)
5V: BLUETOOTH.5, IR-FRONTLEFT.+, IR-FRONTRIGHT.+, IR-SIDELEFT.+, IR-SIDERIGHT.+, M-LEFT.4, M-RIGHT.4, R13.1, U$1.P$10 (5V), U$5.OUT (VOUT), U$8.1 (VIN)
5V1: U$7.P$21 (5V1)
BATTERY_VOLTAGE: R14.2, R15.1, U$7.P$35 (A0)
BLUE-RX: BLUETOOTH.2, U$7.P$6 (A9)
BLUE-TX: BLUETOOTH.3, U$7.P$7 (A10)
BUTTONLEFT: R16.1, U$7.P$8 (A11), UB1.3, UB1.4
BUTTONRIGHT: R21.1, U$7.P$9 (A12), UB2.3, UB2.4
EMITTER_FRONT_LEFT: Q2.1 (G), R4.1, U$7.P$12 (B4)
EMITTER_FRONT_RIGHT: Q4.1 (G), R8.1, U$7.P$37 (C15)
EMITTER_SIDE_LEFT: Q1.1 (G), R2.1, U$7.P$13 (B5)
EMITTER_SIDE_RIGHT: Q3.1 (G), R6.1, U$7.P$38 (C14)
GND: BLUETOOTH.4, M-LEFT.3, M-RIGHT.3, Q1.2 (S), Q2.2 (S), Q3.2 (S), Q4.2 (S), R2.2, R4.2, R6.2, R8.2, R9.2, R10.2, R11.2, R12.2, R15.2, R16.2, R17.2, R18.2, R21.2, U$1.P$2 (GND2), U$1.P$9 (GND1), U$3.GND, U$4.GND, U$4.GND2, U$5.GND, U$7.P$19 (G2), U$7.P$22 (G), U$8.3 (GND), X1.2
GYRO_NCS: U$1.P$3 (SPI-CS), U$7.P$1 (B12)
GYRO_SCL: U$1.P$4 (SPI-SCK), U$7.P$2 (B13)
GYRO_SDA: U$1.P$6 (SPI-MOSI), U$7.P$4 (B15)
GYRO_SDO: U$1.P$5 (SPI-MISO), U$7.P$3 (B14)
IIC_SCL: U$1.P$7 (IIC-SCL), U$7.P$16 (B8)
IIC_SDA: U$1.P$8 (IIC-SDA), U$7.P$17 (B9)
LED-LEFT: LED-LEFT.A, U$7.P$24 (B10)
LED-RIGHT: LED-RIGHT.A, U$7.P$25 (B2)
MDRIVER_IN1: U$3.IN1, U$7.P$29 (A6)
MDRIVER_IN2: U$3.IN2, U$7.P$28 (A7)
MDRIVER_IN3: U$3.IN3, U$7.P$27 (B0)
MDRIVER_IN4: U$3.IN4, U$7.P$26 (B1)
ML+VE: M-LEFT.2, U$3.OUT2
ML-CHA: M-LEFT.6, U$7.P$10 (A15)
ML-CHB: M-LEFT.5, U$7.P$11 (B3)
ML-VE: M-LEFT.1, U$3.OUT1
MR+VE: M-RIGHT.2, U$3.OUT4
MR-CHA: M-RIGHT.6, U$7.P$15 (B7)
MR-CHB: M-RIGHT.5, U$7.P$14 (B6)
MR-VE: M-RIGHT.1, U$3.OUT3
unnamed: IR-FRONTRIGHT.-, R7.1
unnamed: Q1.3 (D), R1.2
unnamed: IR-SIDELEFT.-, R1.1
unnamed: IR-FRONTLEFT.-, R3.1
unnamed: Q2.3 (D), R3.2
unnamed: Q4.3 (D), R7.2
unnamed: IR-SIDERIGHT.-, R5.1
unnamed: Q3.3 (D), R5.2
unnamed: R13.2, U$3.EEP
unnamed: LED-RIGHT.C, R18.1
unnamed: LED-LEFT.C, R17.1
unnamed: R19.2, UB1.1, UB1.2
unnamed: R20.2, UB2.1, UB2.2
unnamed: S1.2, X1.1
RECEIVER_FRONT_LEFT: DET-FRONTLEFT.E, R12.1, U$7.P$30 (A5)
RECEIVER_FRONT_RIGHT: DET-FRONTRIGHT.E, R10.1, U$7.P$33 (A2)
RECEIVER_SIDE_LEFT: DET-SIDELEFT.E, R9.1, U$7.P$31 (A4)
RECEIVER_SIDE_RIGHT: DET-SIDERIGHT.E, R11.1, U$7.P$32 (A3)
VBAT: R14.1, S1.1 (O), U$4.VIN, U$5.IN (VIN)
VMOT: U$3.VCC, U$4.VOUT

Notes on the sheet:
3.7v to 9v
3.7v to 5v
5v to 3.3v

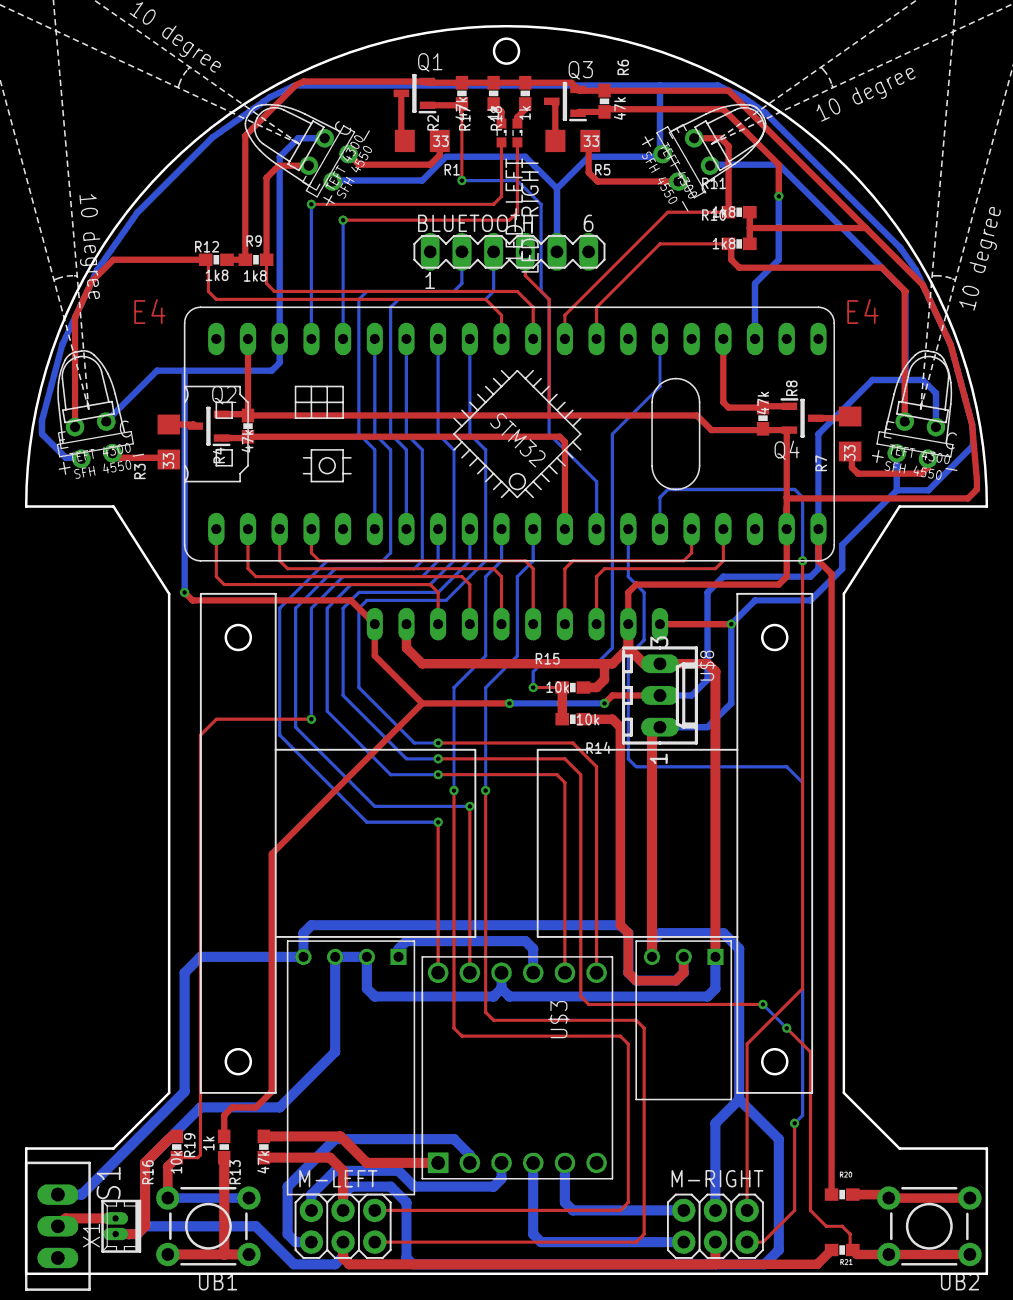
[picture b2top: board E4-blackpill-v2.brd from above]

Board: 2 copper layers, 77.0 x 100.0 mm, 48 parts (0 on the bottom side), 52 nets.

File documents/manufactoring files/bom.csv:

Qty,Designator,Footprint,Comment,LCSC Part # (optional),Description (optional)
1,U$7,BLACK_PILL,do not populate,,stm32 board
2,"LED-LEFT, LED-RIGHT",SML0603,,C125098,green SMD leds
1,BLUETOOTH,MA06-1,do not populate,,HC05 board
2,"M-LEFT, M-RIGHT",2X03,do not populate,,headers
2,"UB1,UB2",TACTILE-PTH,do not populate,,push button switch
4,"R14, R15, R16,R21",0603-RES,,C269701,SMD resistor 0603 package 10k
4,"R9, R10, R11,R12",0603-RES,,C269444,SMD resistor 0603 package 1k8
4,"R17, R18, R19,R20",0603-RES,,C269704,SMD resistor 0603 package 1k
4,"R1, R3, R5, R7",1206,,C325941,SMD resistor 0603 package 33 ohm
5,"R2, R4, R6, R8, R13",0603-RES,,C269715,SMD resistor 0603 package 47k
1,U$3,DRV8833,do not populate,,motor driver board
1,U$1,E4_SPI-IIC,do not populate,,display board
4,"IR-FRONTLEFT, IR-FRONTRIGHT, IR-SIDELEFT, IR-SIDERIGHT",EMITTER,do not populate,,IR emitters
4,"Q1, Q2, Q3, Q4",SOT96P237X111-3N,,C15310,SMD sot23 package FDV301N
4,"DET-FRONTLEFT, DET-FRONTRIGHT, DET-SIDELEFT, DET-SIDERIGHT",RECEIVER,do not populate,,IR detectors
1,S1,TL3XPO,do not populate,,Tiny Switch
1,U$4,BUCK3TO9-HORIZONTAL,do not populate,,BUCK3TO9BUCK3TO9-HORIZONTAL
1,U$5,BUCK3TO5-H,do not populate,,BUCK3TO5
1,U$8,6410-03,do not populate,,3V3-CONV3V3CONV
1,X1,53047-02,do not populate,,53047-02

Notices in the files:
parts and their libraries:
SparkFun: Licensing: CC v3.0 Share-Alike You are welcome to use this library for commercial purposes.
